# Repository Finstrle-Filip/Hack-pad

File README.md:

# Hack-pad
creating my own hack pad

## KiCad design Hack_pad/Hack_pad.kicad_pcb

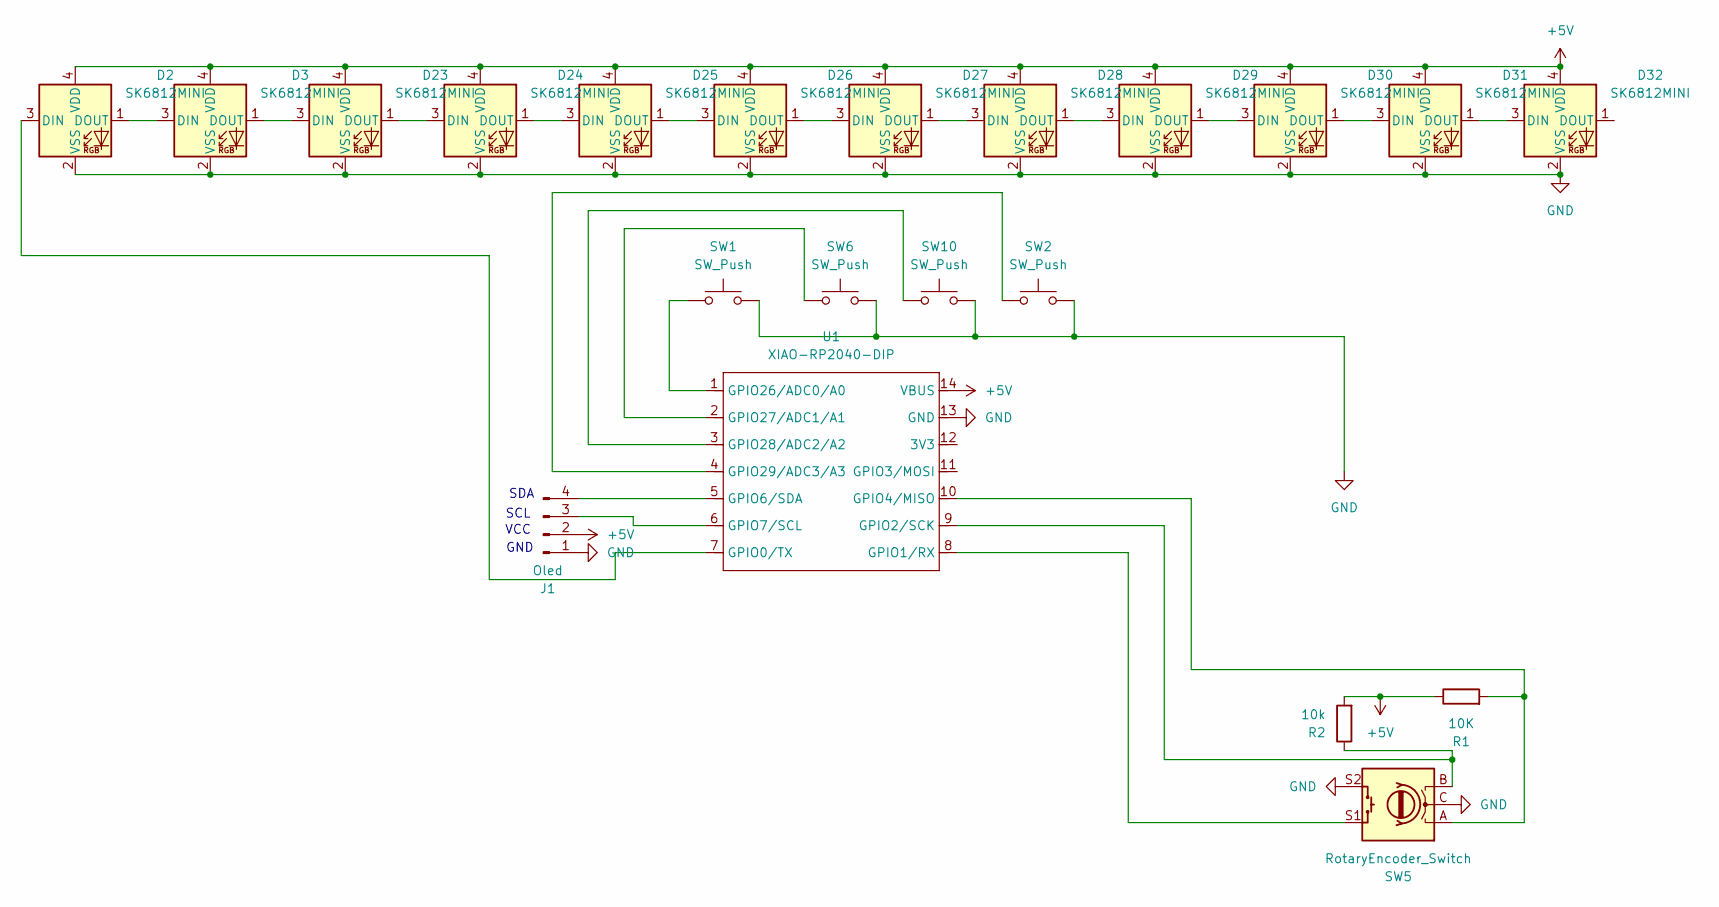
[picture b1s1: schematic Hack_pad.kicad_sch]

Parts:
D2, D3, D23, D24, D25, D26, D27, D28, D29, D30, D31, D32: SK6812MINI; LED_SK6812MINI_PLCC4_3.5x3.5mm_P1.75mm
J1: Oled; SSD1306-0.91-OLED-4pin-128x32
R1: 10K; R_0201_0603Metric_Pad0.64x0.40mm_HandSolder
R2: 10k; R_0201_0603Metric_Pad0.64x0.40mm_HandSolder
SW1, SW2, SW6, SW10: SW_Push; SW_Cherry_MX_1.00u_PCB
SW5: RotaryEncoder_Switch; RotaryEncoder_Alps_EC11E-Switch_Vertical_H20mm
U1: XIAO-RP2040-DIP

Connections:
+5V: D2.4 (VDD), D3.4 (VDD), D23.4 (VDD), D24.4 (VDD), D25.4 (VDD), D26.4 (VDD), D27.4 (VDD), D28.4 (VDD), D29.4 (VDD), D30.4 (VDD), D31.4 (VDD), D32.4 (VDD), J1.2, R1.1, R2.2, U1.14 (VBUS)
GND: D2.2 (VSS), D3.2 (VSS), D23.2 (VSS), D24.2 (VSS), D25.2 (VSS), D26.2 (VSS), D27.2 (VSS), D28.2 (VSS), D29.2 (VSS), D30.2 (VSS), D31.2 (VSS), D32.2 (VSS), J1.1, SW1.2, SW2.2, SW5.C, SW5.S2, SW6.2, SW10.2, U1.13 (GND)
unnamed: D2.3 (DIN), U1.7 (GPIO0/TX)
unnamed: D2.1 (DOUT), D3.3 (DIN)
unnamed: D3.1 (DOUT), D23.3 (DIN)
unnamed: D23.1 (DOUT), D24.3 (DIN)
unnamed: D24.1 (DOUT), D25.3 (DIN)
unnamed: D25.1 (DOUT), D26.3 (DIN)
unnamed: D26.1 (DOUT), D27.3 (DIN)
unnamed: D27.1 (DOUT), D28.3 (DIN)
unnamed: D28.1 (DOUT), D29.3 (DIN)
unnamed: D29.1 (DOUT), D30.3 (DIN)
unnamed: D30.1 (DOUT), D31.3 (DIN)
unnamed: D31.1 (DOUT), D32.3 (DIN)
unnamed: J1.3, U1.6 (GPIO7/SCL)
unnamed: J1.4, U1.5 (GPIO6/SDA)
unnamed: SW5.S1, U1.8 (GPIO1/RX)
unnamed: R2.1, SW5.B, U1.9 (GPIO2/SCK)
unnamed: R1.2, SW5.A, U1.10 (GPIO4/MISO)
unnamed: SW1.1, U1.1 (GPIO26/ADC0/A0)
unnamed: SW6.1, U1.2 (GPIO27/ADC1/A1)
unnamed: SW10.1, U1.3 (GPIO28/ADC2/A2)
unnamed: SW2.1, U1.4 (GPIO29/ADC3/A3)

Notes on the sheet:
VCC
GND
SDA
SCL

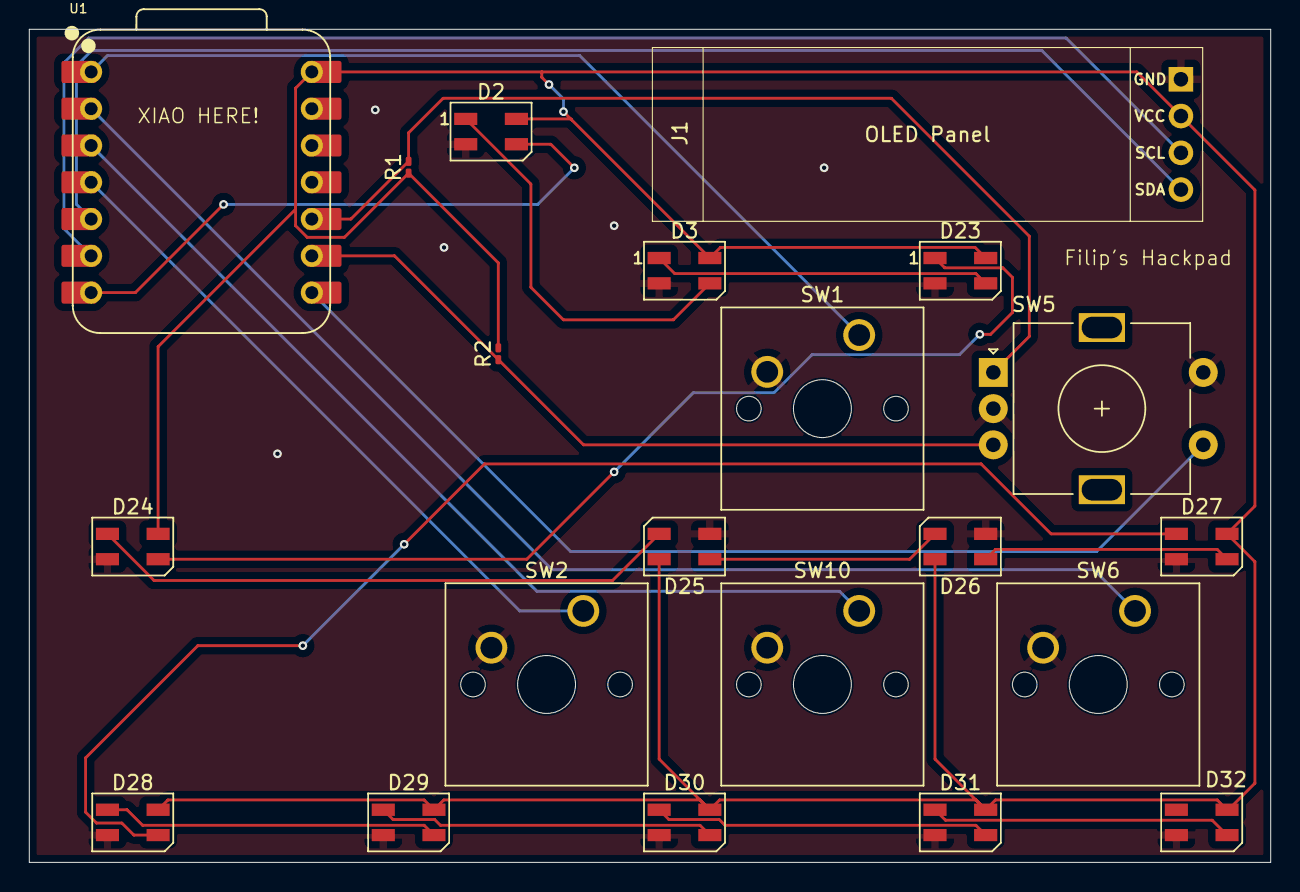
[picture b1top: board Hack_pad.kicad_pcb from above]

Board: 2 copper layers, 85.7 x 57.5 mm, 21 parts (0 on the bottom side), 23 nets.

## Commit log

2025-12-04 Adding my schematicks
    Im adding my chematicks of my hack pad
2025-12-04 Delete Hack_pad.kicad_pcb
    missplaced
2025-12-04 update pcb
2025-12-06 fix errors
2025-12-08 case
2025-12-09 update
    recrated
2025-12-09 Finished_case
